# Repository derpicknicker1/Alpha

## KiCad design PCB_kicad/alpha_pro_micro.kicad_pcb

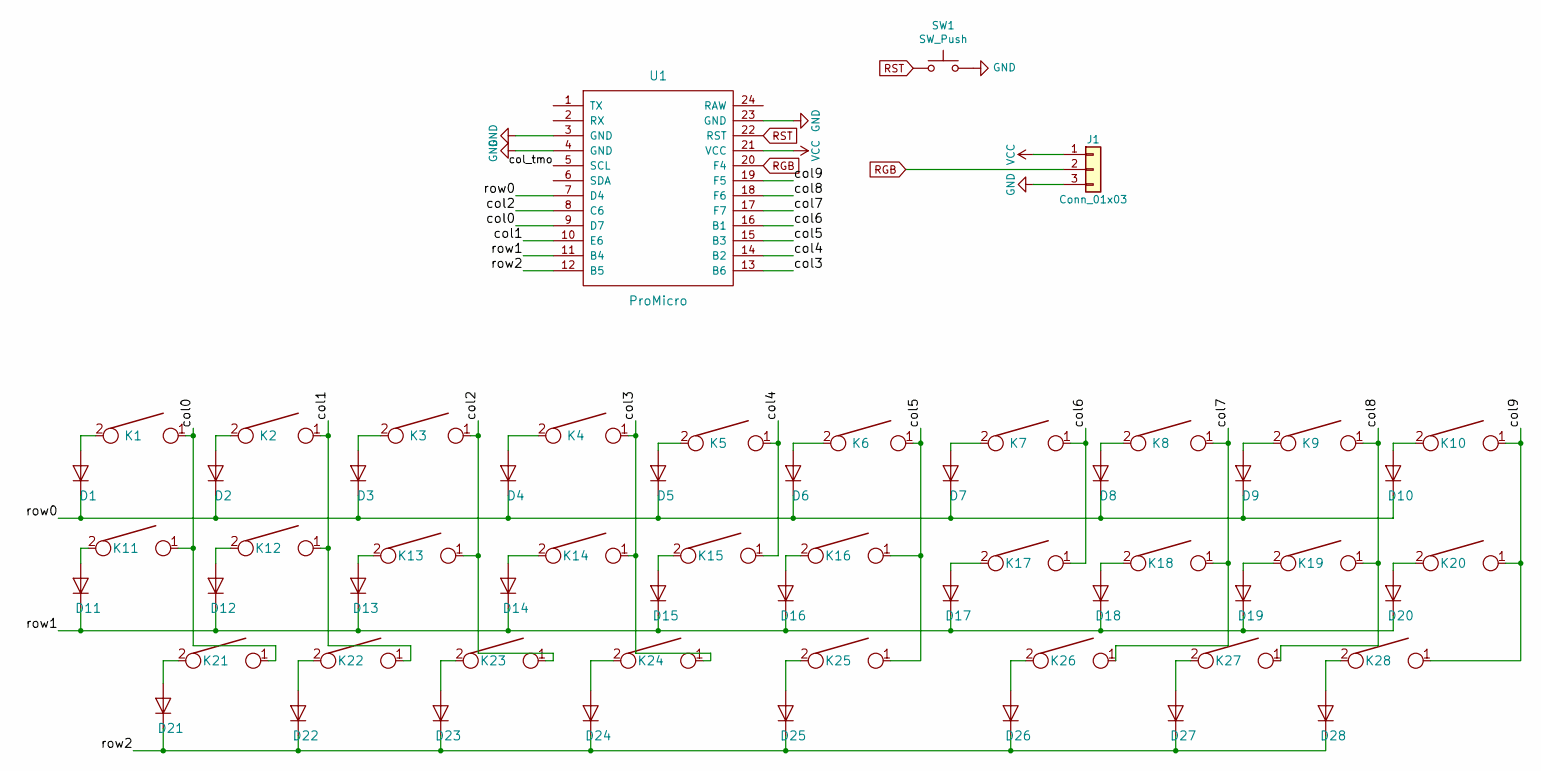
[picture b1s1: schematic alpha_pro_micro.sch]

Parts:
D1, D2, D3, D4, D5, D6, D7, D8, D9, D10, D11, D12, D13, D14, D15, D16, D17, D18, D19, D20, D21, D22, D23, D24, D25, D26, D27, D28: D; ComboDiode
J1: Conn_01x03; Pin_Header_Straight_1x03_Pitch2.54mm
K1, K2, K3, K4, K5, K6, K7, K8, K9, K10, K11, K12, K13, K14, K15, K16, K17, K18, K19, K20, K21, K22, K23, K24, K26, K27, K28: KEYSW; MXOnly-1U-NoLED
K25: KEYSW; MXOnly-2U-ReversedStabilizers-NoLED
SW1: SW_Push; SKQG-1155865
U1: ProMicro

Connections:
/col0: K1.1, K11.1, K21.1, U1.9 (D7)
/col1: K2.1, K12.1, K22.1, U1.10 (E6)
/col2: K3.1, K13.1, K23.1, U1.8 (C6)
/col3: K4.1, K14.1, K24.1, U1.13 (B6)
/col4: K5.1, K15.1, U1.14 (B2)
/col5: K6.1, K16.1, K25.1, U1.15 (B3)
/col6: K7.1, K17.1, U1.16 (B1)
/col7: K8.1, K18.1, K26.1, U1.17 (F7)
/col8: K9.1, K19.1, K27.1, U1.18 (F6)
/col9: K10.1, K20.1, K28.1, U1.19 (F5)
/col_tmo: U1.5 (SCL)
/row0: D1.1 (K), D2.1 (K), D3.1 (K), D4.1 (K), D5.1 (K), D6.1 (K), D7.1 (K), D8.1 (K), D9.1 (K), D10.1 (K), U1.7 (D4)
/row1: D11.1 (K), D12.1 (K), D13.1 (K), D14.1 (K), D15.1 (K), D16.1 (K), D17.1 (K), D18.1 (K), D19.1 (K), D20.1 (K), U1.11 (B4)
/row2: D21.1 (K), D22.1 (K), D23.1 (K), D24.1 (K), D25.1 (K), D26.1 (K), D27.1 (K), D28.1 (K), U1.12 (B5)
GND: J1.3, SW1.2, U1.3 (GND), U1.4 (GND), U1.23 (GND)
unnamed: D1.2 (A), K1.2
unnamed: D2.2 (A), K2.2
unnamed: D3.2 (A), K3.2
unnamed: D4.2 (A), K4.2
unnamed: D5.2 (A), K5.2
unnamed: D6.2 (A), K6.2
unnamed: D7.2 (A), K7.2
unnamed: D8.2 (A), K8.2
unnamed: D9.2 (A), K9.2
unnamed: D10.2 (A), K10.2
unnamed: D11.2 (A), K11.2
unnamed: D12.2 (A), K12.2
unnamed: D13.2 (A), K13.2
unnamed: D14.2 (A), K14.2
unnamed: D15.2 (A), K15.2
unnamed: D16.2 (A), K16.2
unnamed: D17.2 (A), K17.2
unnamed: D18.2 (A), K18.2
unnamed: D19.2 (A), K19.2
unnamed: D20.2 (A), K20.2
unnamed: D21.2 (A), K21.2
unnamed: D22.2 (A), K22.2
unnamed: D23.2 (A), K23.2
unnamed: D24.2 (A), K24.2
unnamed: D25.2 (A), K25.2
unnamed: D26.2 (A), K26.2
unnamed: D27.2 (A), K27.2
unnamed: D28.2 (A), K28.2
RGB: J1.2, U1.20 (F4)
RST: SW1.1, U1.22 (RST)
VCC: J1.1, U1.21 (VCC)

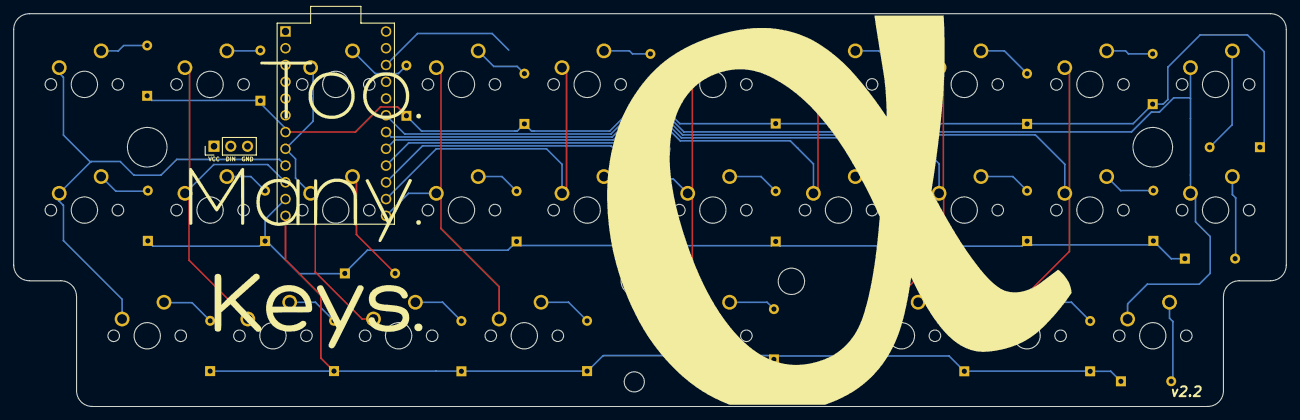
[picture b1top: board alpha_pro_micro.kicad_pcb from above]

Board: 2 copper layers, 192.9 x 59.5 mm, 60 parts (1 on the bottom side), 45 nets.

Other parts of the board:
HC1: MountingHole_6mm

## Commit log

2021-05-06 Added info of how to generate a plate
2021-05-07 Begin PCB rework
